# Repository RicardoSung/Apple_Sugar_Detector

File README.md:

# Apple Sugar Detector
> Apple sugar detector is a complete set of the construction of DIYed brix hydrometer targeted on Apples.

## Installation

* Prerequisites:
   *  Autodesk Inventor 2020 +
   *  Cadence OrCAD Alllegro 17.4 +
   *  Xilinx ISE Designer 14.7 +
   *  Python 3.8 
   *  Tensorflow 2.5.0   
   *  [usb-serial-for-android](https://github.com/mik3y/usb-serial-for-android#:~:text=usb-serial-for-android%20This%20is%20a%20driver%20library%20for%20communication,are%20required%3B%20all%20drivers%20are%20implemented%20in%20Java.) library

For installable APK, please direct to `release`.

## Usage example

TBD

## Release History

### 0.x Internal Version

* 0.0.1
    * Work in progress, framework uploaded
* 0.1
    * PCB design first version uploaded
    * External structure first version uploaded
    * Android application first version uploaded
* 0.2
    * PCB design second version uploaded
    * External structure second version uploaded
    * Android application second version uploaded
    * Optic simulation first version uploaded
* 0.3
    * Neural network first version uploaded
    * External structure third version uploaded
    * Optic simulation second version uploaded
* 0.4
    * Optic simulation third version uploaded
    * 3D printing first version
* 0.5
    * Optic simulation fourth version uploaded
    * 3D printing second version
    * First training dataset acquired 

## Meta

Distributed under the GPL license. See ``LICENSE`` for more information.

## Contributing

1. Fork it (<https://github.com/GeekerRicardo/fruit_companion/fork>)
2. Create your feature branch (`git checkout -b feature/fooBar`)
3. Commit your changes (`git commit -am 'Add some fooBar'`)
4. Push to the branch (`git push origin feature/fooBar`)
5. Create a new Pull Request

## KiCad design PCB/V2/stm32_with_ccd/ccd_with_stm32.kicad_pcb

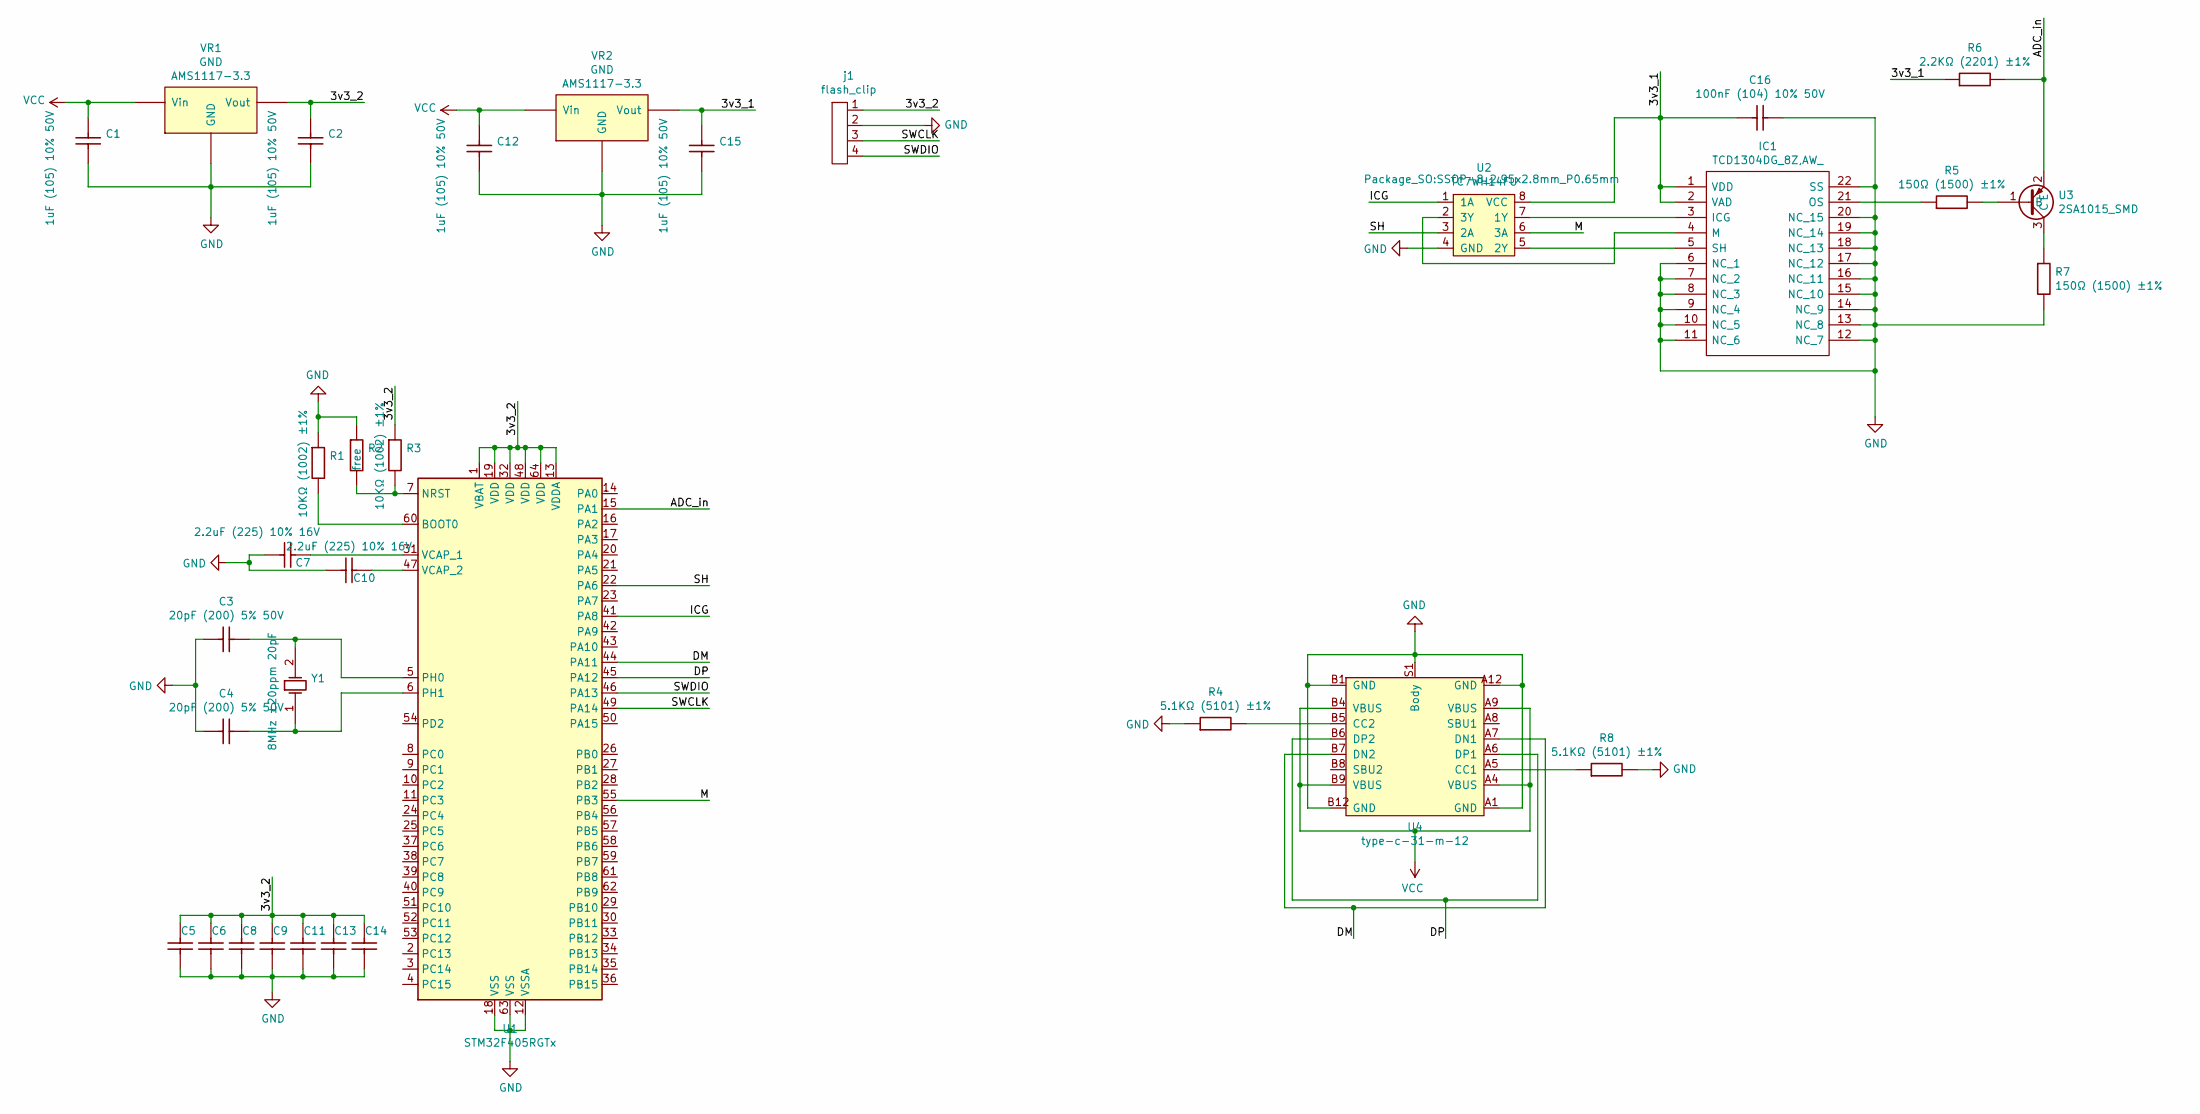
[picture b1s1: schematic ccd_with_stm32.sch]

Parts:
C1, C2, C12, C14, C15: 0603_1uF__105_10%_50V; 0603_C
C3, C4: 0603_20pF__200_5%_50V; 0603_C
C5, C6, C8, C9, C11, C13, C16: 0603_100nF__104_10%_50V; 0603_C
C7, C10: 0603_2.2uF__225_10%_16V; 0603_C
IC1: TCD1304DG_8Z,AW_; DIP1016W62P254L4160H372Q22N; Manufacturer_Part_Number TCD1304DG(8Z,AW); Mouser Part Number 757-TCD1304DG8ZAW
R1, R3: 0603_10KΩ__1002_1%; 0603_R
R2: 0402_1.2KΩ__1201_1%; 0402_R
R4, R8: 0603_5.1KΩ__5101_1%; 0603_R
R5, R7: 0603_150Ω__1500_1%; 0603_R
R6: 0603_2.2KΩ__2201_1%; 0603_R
U1: STM32F405RGTx; LQFP-64_10x10mm_P0.5mm
U2: TC7WH14FU; SSOP-8_2.95x2.8mm_P0.65mm
U3: 2SA1015_SMD; SOT-23(SOT-23-3)
U4: type-c-31-m-12; USB_C_Receptacle_HRO_TYPE-C-31-M-12
VR1, VR2: SOT-223_AMS1117-3.3; SOT-223
Y1: SMD-5032_2P_8MHz_20ppm_20pF; SMD-5032_2P
j1: flash_clip

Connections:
/3v3_1: C15.1, C16.1, IC1.1 (VDD), IC1.2 (VAD), R6.1, U2.8 (VCC), VR2.2 (Vout)
/3v3_2: C2.1, C5.1, C6.1, C8.1, C9.1, C11.1, C13.1, C14.1, R3.1, U1.1 (VBAT), U1.13 (VDDA), U1.19 (VDD), U1.32 (VDD), U1.48 (VDD), U1.64 (VDD), VR1.2 (Vout), j1.1
/ADC_in: R6.2, U1.15 (PA1), U3.2 (E)
/DM: U1.44 (PA11), U4.A7 (DN1), U4.B7 (DN2)
/DP: U1.45 (PA12), U4.A6 (DP1), U4.B6 (DP2)
/ICG: U1.41 (PA8), U2.1 (1A)
/M: U1.55 (PB3), U2.6 (3A)
/SH: U1.22 (PA6), U2.3 (2A)
/SWCLK: U1.49 (PA14), j1.3
/SWDIO: U1.46 (PA13), j1.4
GND: C1.2, C2.2, C3.1, C4.1, C5.2, C6.2, C7.1, C8.2, C9.2, C10.1, C11.2, C12.2, C13.2, C14.2, C15.2, C16.2, IC1.6 (NC_1), IC1.7 (NC_2), IC1.8 (NC_3), IC1.9 (NC_4), IC1.10 (NC_5), IC1.11 (NC_6), IC1.12 (NC_7), IC1.13 (NC_8), IC1.14 (NC_9), IC1.15 (NC_10), IC1.16 (NC_11), IC1.17 (NC_12), IC1.18 (NC_13), IC1.19 (NC_14), IC1.20 (NC_15), IC1.22 (SS), R1.1, R2.1, R4.1, R7.2, R8.2, U1.12 (VSSA), U1.18 (VSS), U1.63 (VSS), U2.4 (GND), U4.A1 (GND), U4.A12 (GND), U4.B1 (GND), U4.B12 (GND), U4.S1 (Body), VR1.1 (GND), VR2.1 (GND), j1.2
unnamed: C3.2, U1.5 (PH0), Y1.2 (OSC2)
unnamed: C4.2, U1.6 (PH1), Y1.1 (OSC1)
unnamed: C7.2, U1.31 (VCAP_1)
unnamed: C10.2, U1.47 (VCAP_2)
unnamed: IC1.3 (ICG), U2.7 (1Y)
unnamed: IC1.4 (M), U2.2 (3Y)
unnamed: IC1.5 (SH), U2.5 (2Y)
unnamed: IC1.21 (OS), R5.1
unnamed: R1.2, U1.60 (BOOT0)
unnamed: R2.2, R3.2, U1.7 (NRST)
unnamed: R4.2, U4.B5 (CC2)
unnamed: R5.2, U3.1 (B)
unnamed: R7.1, U3.3 (C)
unnamed: R8.1, U4.A5 (CC1)
VCC: C1.1, C12.1, U4.A4 (VBUS), U4.A9 (VBUS), U4.B4 (VBUS), U4.B9 (VBUS), VR1.3 (Vin), VR2.3 (Vin)

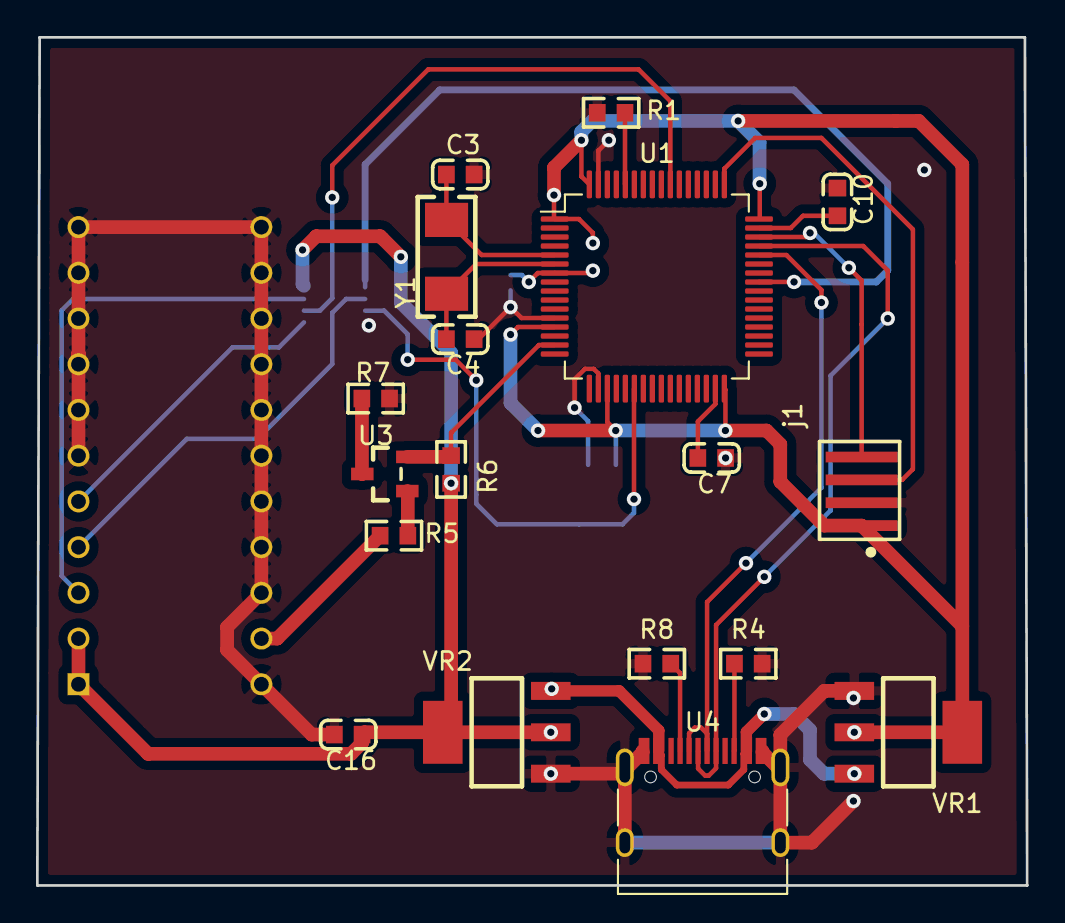
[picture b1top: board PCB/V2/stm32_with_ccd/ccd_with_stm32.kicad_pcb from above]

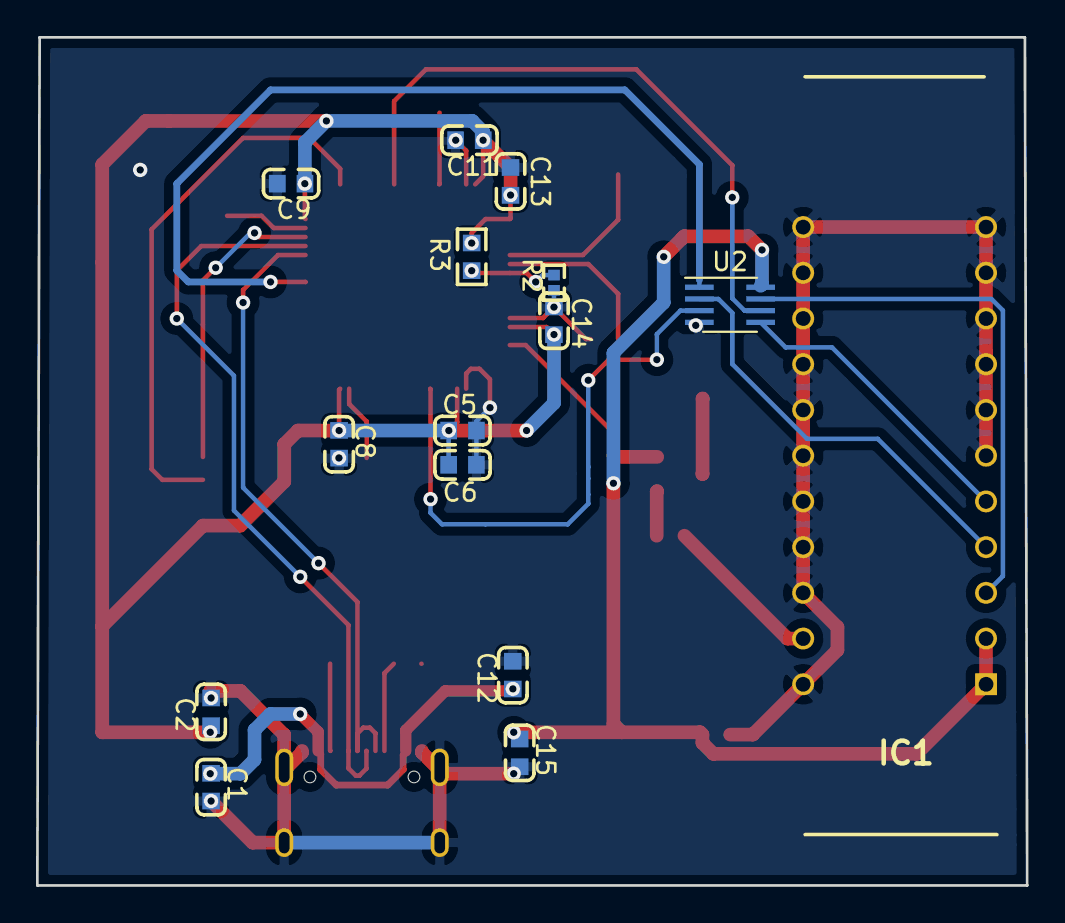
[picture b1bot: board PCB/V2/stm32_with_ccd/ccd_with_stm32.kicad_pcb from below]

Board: 2 copper layers, 55.0 x 47.1 mm, 33 parts (15 on the bottom side), 26 nets.

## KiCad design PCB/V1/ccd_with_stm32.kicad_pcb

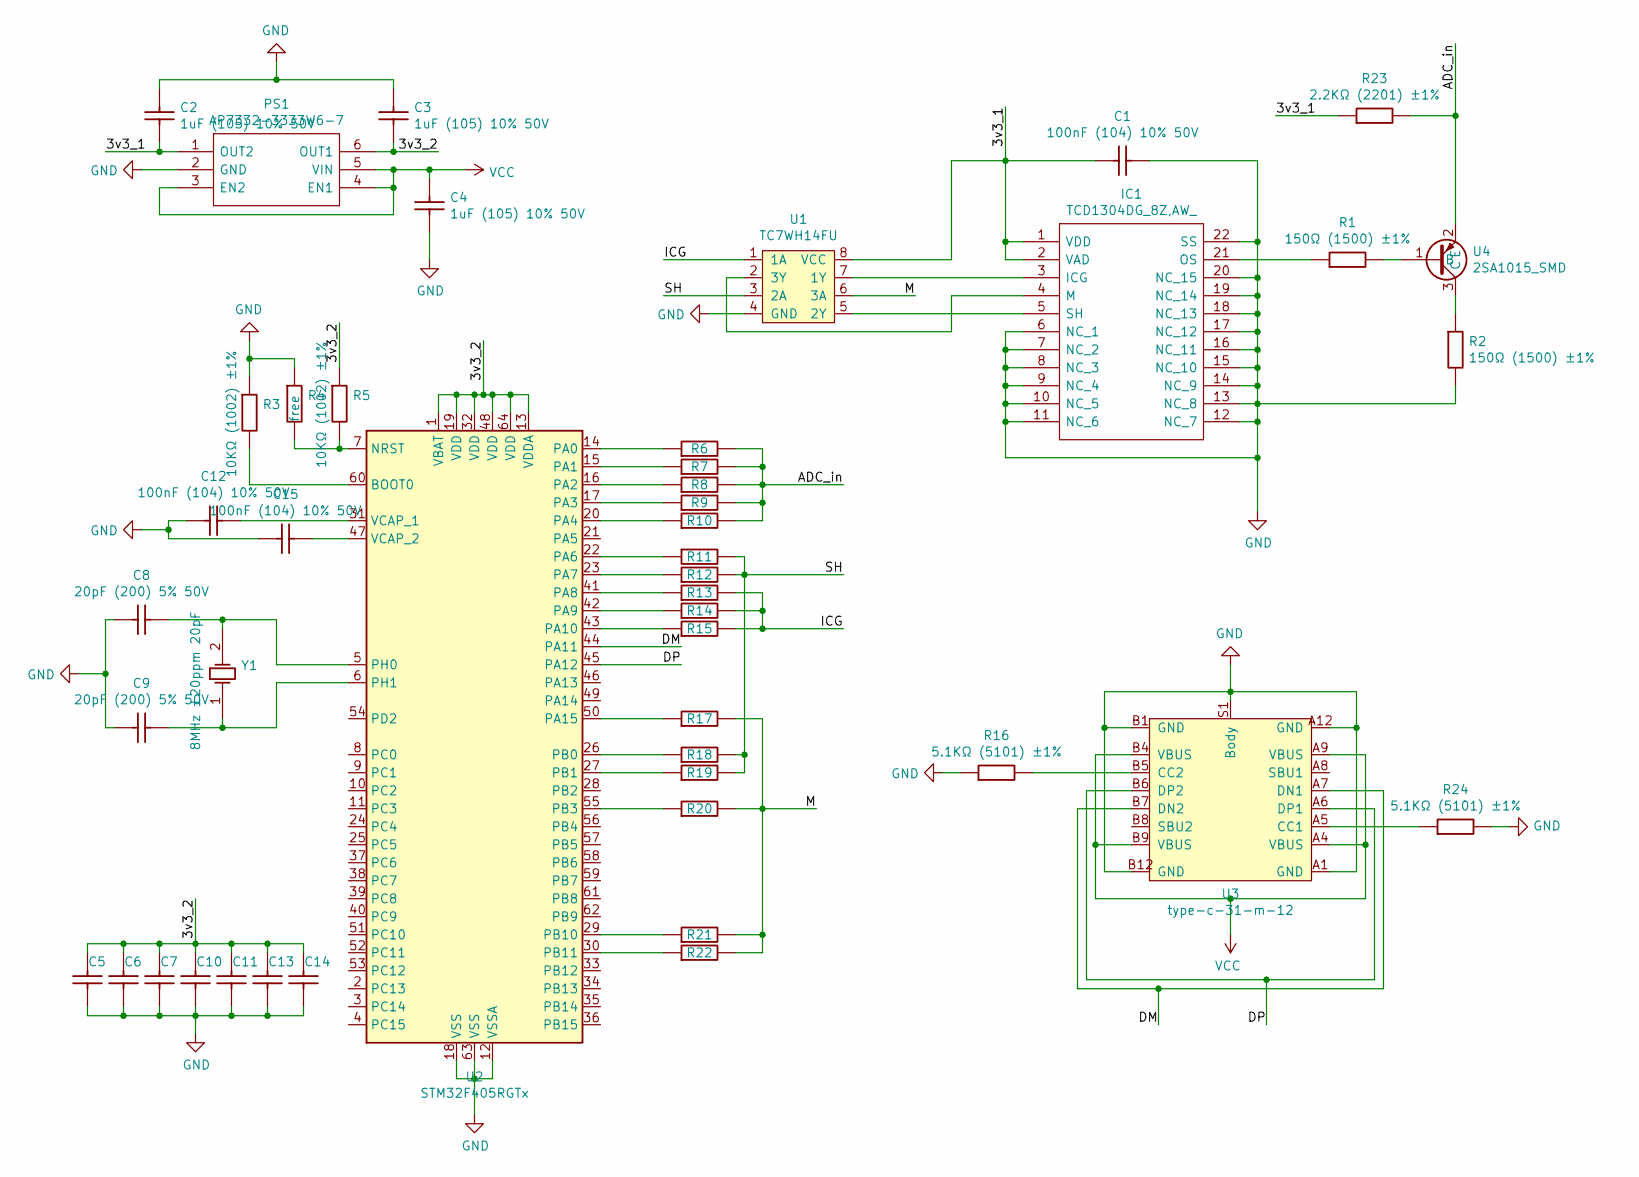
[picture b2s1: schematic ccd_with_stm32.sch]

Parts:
C1, C5, C6, C7, C10, C11, C12, C13, C15: 0603_100nF__104_10%_50V; 0603_C
C2, C3, C4, C14: 0603_1uF__105_10%_50V; 0603_C
C8, C9: 0603_20pF__200_5%_50V; 0603_C
IC1: TCD1304DG_8Z,AW_; DIP1016W62P254L4160H372Q22N; Manufacturer_Part_Number TCD1304DG(8Z,AW); Mouser Part Number 757-TCD1304DG8ZAW
PS1: AP7332-3333W6-7; SOT95P275X110-6N; Manufacturer_Part_Number AP7332-3333W6-7; Mouser Part Number 621-AP7332-3333W6-7
R1, R2: 0603_150Ω__1500_1%; 0603_R
R3, R5: 0603_10KΩ__1002_1%; 0603_R
R4: 0402_1.2KΩ__1201_1%; 0402_R
R6, R7, R8, R9, R10, R11, R12, R13, R14, R15, R17, R18, R19, R20, R21, R22: 0402_0Ω__0R0_1%; 0402_R
R16, R24: 0603_5.1KΩ__5101_1%; 0603_R
R23: 0603_2.2KΩ__2201_1%; 0603_R
U1: TC7WH14FU; SOP65P640X120-8N
U2: STM32F405RGTx; LQFP-64_10x10mm_P0.5mm
U3: type-c-31-m-12; USB_C_Receptacle_HRO_TYPE-C-31-M-12
U4: 2SA1015_SMD; SOT-23(SOT-23-3)
Y1: SMD-5032_2P_8MHz_20ppm_20pF; SMD-5032_2P

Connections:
/3v3_1: C1.1, C2.2, IC1.1 (VDD), IC1.2 (VAD), PS1.1 (OUT2), R23.1, U1.8 (VCC)
/3v3_2: C3.2, C5.1, C6.1, C7.1, C10.1, C11.1, C13.1, C14.1, PS1.6 (OUT1), R5.1, U2.1 (VBAT), U2.13 (VDDA), U2.19 (VDD), U2.32 (VDD), U2.48 (VDD), U2.64 (VDD)
/ADC_in: R6.2, R7.2, R8.2, R9.2, R10.2, R23.2, U4.2 (E)
/DM: U2.44 (PA11), U3.A7 (DN1), U3.B7 (DN2)
/DP: U2.45 (PA12), U3.A6 (DP1), U3.B6 (DP2)
/ICG: R13.2, R14.2, R15.2, U1.1 (1A)
/M: R17.2, R20.2, R21.2, R22.2, U1.6 (3A)
/SH: R11.2, R12.2, R18.2, R19.2, U1.3 (2A)
GND: C1.2, C2.1, C3.1, C4.2, C5.2, C6.2, C7.2, C8.1, C9.1, C10.2, C11.2, C12.1, C13.2, C14.2, C15.1, IC1.6 (NC_1), IC1.7 (NC_2), IC1.8 (NC_3), IC1.9 (NC_4), IC1.10 (NC_5), IC1.11 (NC_6), IC1.12 (NC_7), IC1.13 (NC_8), IC1.14 (NC_9), IC1.15 (NC_10), IC1.16 (NC_11), IC1.17 (NC_12), IC1.18 (NC_13), IC1.19 (NC_14), IC1.20 (NC_15), IC1.22 (SS), PS1.2 (GND), R2.2, R3.1, R4.1, R16.1, R24.2, U1.4 (GND), U2.12 (VSSA), U2.18 (VSS), U2.63 (VSS), U3.A1 (GND), U3.A12 (GND), U3.B1 (GND), U3.B12 (GND), U3.S1 (Body)
unnamed: C8.2, U2.5 (PH0), Y1.2 (OSC2)
unnamed: C9.2, U2.6 (PH1), Y1.1 (OSC1)
unnamed: C12.2, U2.31 (VCAP_1)
unnamed: C15.2, U2.47 (VCAP_2)
unnamed: IC1.3 (ICG), U1.7 (1Y)
unnamed: IC1.4 (M), U1.2 (3Y)
unnamed: IC1.5 (SH), U1.5 (2Y)
unnamed: IC1.21 (OS), R1.1
unnamed: R1.2, U4.1 (B)
unnamed: R2.1, U4.3 (C)
unnamed: R3.2, U2.60 (BOOT0)
unnamed: R4.2, R5.2, U2.7 (NRST)
unnamed: R6.1, U2.14 (PA0)
unnamed: R7.1, U2.15 (PA1)
unnamed: R8.1, U2.16 (PA2)
unnamed: R9.1, U2.17 (PA3)
unnamed: R10.1, U2.20 (PA4)
unnamed: R11.1, U2.22 (PA6)
unnamed: R12.1, U2.23 (PA7)
unnamed: R13.1, U2.41 (PA8)
unnamed: R14.1, U2.42 (PA9)
unnamed: R15.1, U2.43 (PA10)
unnamed: R16.2, U3.B5 (CC2)
unnamed: R17.1, U2.50 (PA15)
unnamed: R18.1, U2.26 (PB0)
unnamed: R19.1, U2.27 (PB1)
unnamed: R20.1, U2.55 (PB3)
unnamed: R21.1, U2.29 (PB10)
unnamed: R22.1, U2.30 (PB11)
unnamed: R24.1, U3.A5 (CC1)
VCC: C4.1, PS1.3 (EN2), PS1.4 (EN1), PS1.5 (VIN), U3.A4 (VBUS), U3.A9 (VBUS), U3.B4 (VBUS), U3.B9 (VBUS)

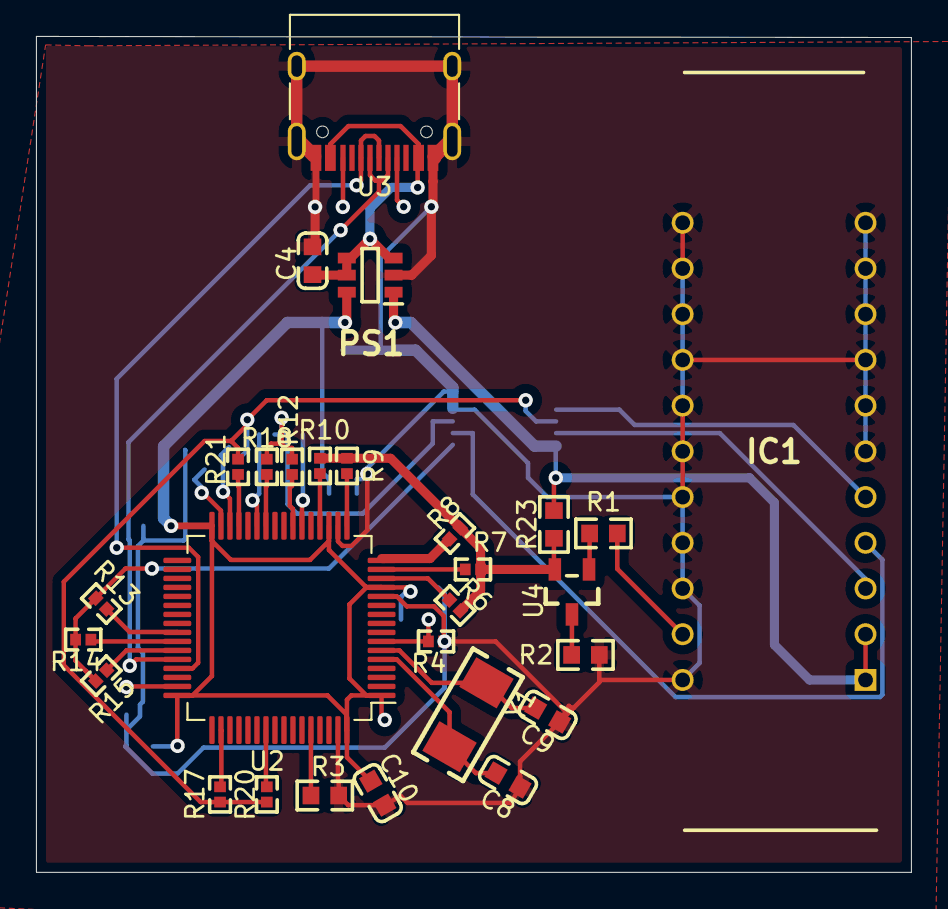
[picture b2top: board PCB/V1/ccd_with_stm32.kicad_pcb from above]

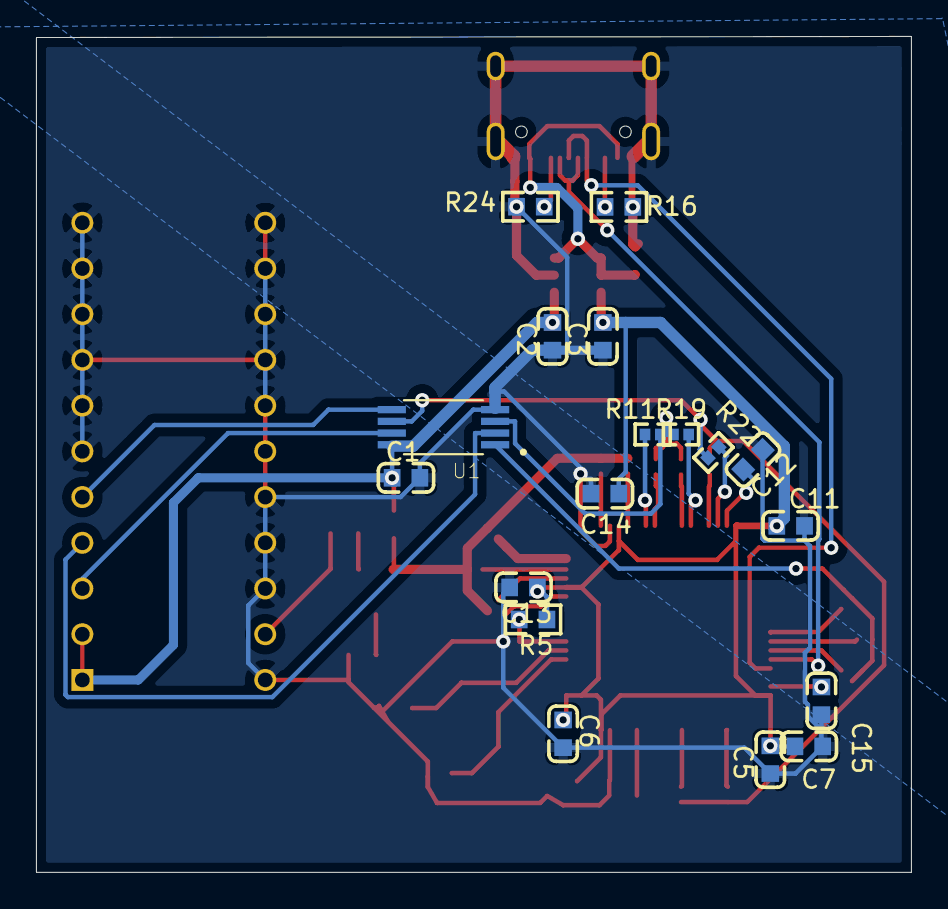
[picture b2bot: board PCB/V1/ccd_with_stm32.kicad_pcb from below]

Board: 2 copper layers, 48.6 x 46.4 mm, 46 parts (18 on the bottom side), 40 nets.

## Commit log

2021-05-13 initial commit
    Initial commit. ONLY framework.
2021-05-13 directory remap
2021-05-13 directory remap #2
2021-05-13 pcb file added
2021-05-15 pcb v2
2021-07-12 update pcb & verilog code
2021-07-12 update structure
2021-07-12 change the name of Structure_Design file director
2021-07-12 Create LICENSE
2021-07-12 Android Application update
2021-07-12 neural network update
2021-07-12 update zemax simulation
2021-09-03 uploaded apple datasets, neural networks
2021-09-03 add reports
